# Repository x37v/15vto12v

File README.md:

# 15v to 12v biopolar

Based on design by [mangros](https://www.muffwiggler.com/forum/viewtopic.php?t=133086&start=0&postdays=0&postorder=asc&highlight=).

## BOM

* 5 22uF electro caps, 20v
* 5 100nF ceramic caps, 20v
* 1 L7812
* 1 L7912
* 1 L7805
* connectors as needed

## Oshpark link

[https://oshpark.com/shared_projects/xNlaxGj8](https://oshpark.com/shared_projects/xNlaxGj8)

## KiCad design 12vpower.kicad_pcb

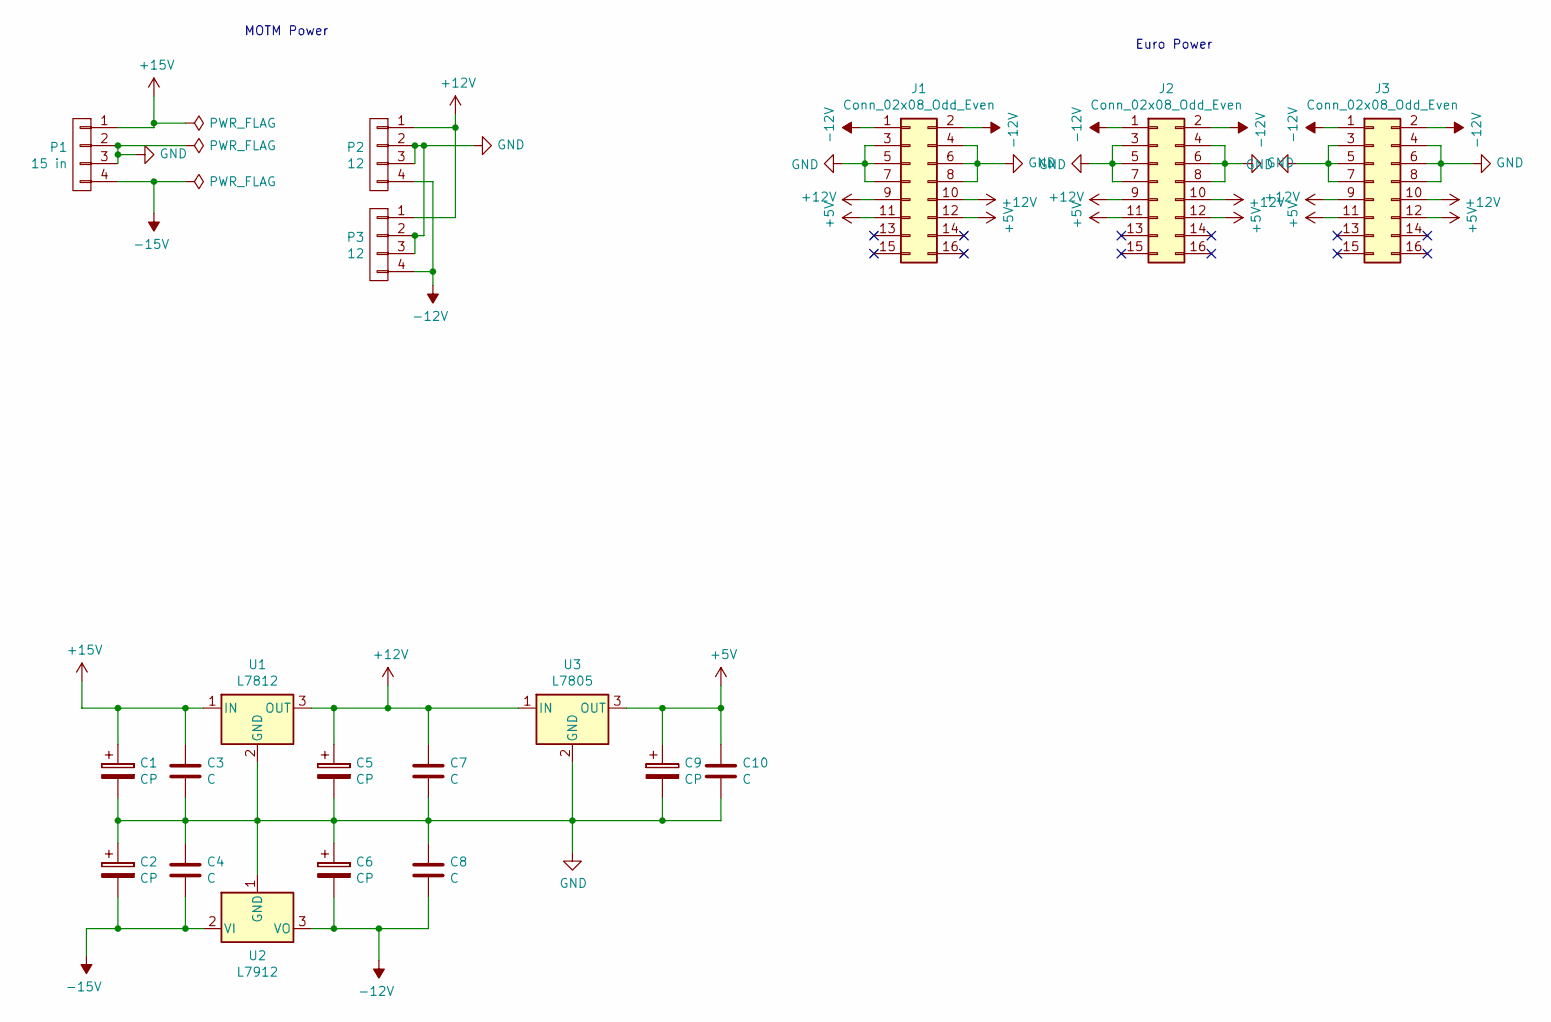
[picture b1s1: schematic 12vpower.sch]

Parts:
C1, C2, C5, C6, C9: CP; CP_Radial_D7.5mm_P2.50mm
C3, C4, C7, C8, C10: C; C_Disc_D4.3mm_W1.9mm_P5.00mm
J1, J2, J3: Conn_02x08_Odd_Even; PinHeader_2x08_P2.54mm_Vertical
P1: 15 in; MTA-156-4
P2, P3: 12; MTA-156-4
U1: L7812; TO-220-3_Vertical
U2: L7912; TO-220-3_Vertical
U3: L7805; TO-220-3_Vertical

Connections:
+5V: C9.1, C10.1, J1.11, J1.12, J2.11, J2.12, J3.11, J3.12, U3.3 (OUT)
+12V: C5.1, C7.1, J1.9, J1.10, J2.9, J2.10, J3.9, J3.10, P2.1, P3.1, U1.3 (OUT), U3.1 (IN)
+15V: C1.1, C3.1, P1.1, U1.1 (IN)
-12V: C6.2, C8.2, J1.1, J1.2, J2.1, J2.2, J3.1, J3.2, P2.4, P3.4, U2.3 (VO)
-15V: C2.2, C4.2, P1.4, U2.2 (VI)
GND: C1.2, C2.1, C3.2, C4.1, C5.2, C6.1, C7.2, C8.1, C9.2, C10.2, J1.3, J1.4, J1.5, J1.6, J1.7, J1.8, J2.3, J2.4, J2.5, J2.6, J2.7, J2.8, J3.3, J3.4, J3.5, J3.6, J3.7, J3.8, P1.2, P1.3, P2.2, P2.3, P3.2, P3.3, U1.2 (GND), U2.1 (GND), U3.2 (GND)

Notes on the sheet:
Euro Power
MOTM Power

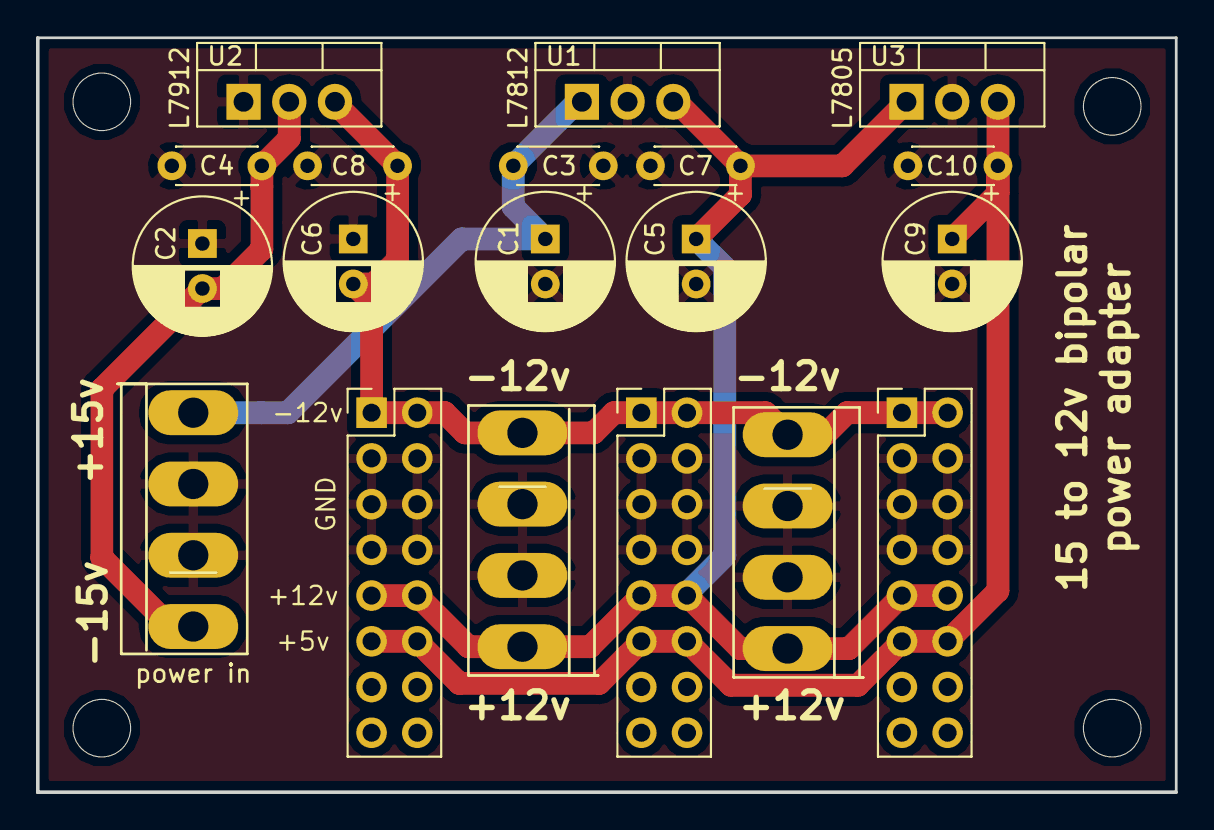
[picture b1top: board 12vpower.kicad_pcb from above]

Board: 2 copper layers, 63.2 x 41.9 mm, 19 parts (0 on the bottom side), 6 nets.

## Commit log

2019-03-16 schematic layout
2019-03-16 labels and more euro power
2019-03-16 footprints
2019-03-16 forgot euro ground
2019-03-16 most of the layout should be done
2019-03-18 moved a few things around, updated labels
2019-03-18 label movement
2019-04-23 ignore csv
2019-04-23 readme
2022-12-17 added oshpark link
